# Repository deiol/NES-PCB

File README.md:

# NES-PCB
Based on a request and discussion in this [r/NES thread](https://www.reddit.com/r/nes/comments/1rh8xvy/looking_for_replacement_powereject_boards/), I created a drop-in replacement for the Power/Reset PCB from the front-loader Nintendo Entertainment System.

# PCB Differences
Taking a look at pictures online as well as NES consoles I had available, I realized there are at least two board revisions; NES-SW-01 and NES-SW-02 (if you've come across any other variants, please let me know). 

**NES-SW-01**

**NES-SW-02**

This design is based on the NES-SW-02 as it should be "backwards compatible" with the NES-SW-01.

Additionally, I used the same power switch footprint for the reset switch. This way you should be able to use either switch body type for the reset switch (although you'll want to use a momentary switch for reset, latching for power).

# Board Production
Board thickness is 1.6mm. [Gerber and drill files](https://github.com/deiol/NES-PCB/tree/main/Gerbers) are included in case they are helpful to anyone. They were created for production at JLCPCB following their gudiance on [generating Gerber and Drill files in KiCAD 9](https://jlcpcb.com/help/article/how-to-generate-gerber-and-drill-files-in-kicad-9). I only reference JLCPCB because I have used them in the past. You can of course have the board produced by a different manufacturer, some aspects of the board may need to be tweaked based on *their* requirements.

If you don't want to go through the trouble of getting boards manufactured, they are available for sale on [Tindie](https://www.tindie.com/products/deiol/nes-replacement-powerreset-switch-pcb/) or [Ko-fi](https://ko-fi.com/s/01c29a42ff)

# Disclaimer
I am not an electrical engineer, just a hobbyist. I couldn't find datasheets for any of the components, so the footprints were created from "scratch" using measurements taken with rulers and calipers. Similarly, the boards were measured with rulers and calipers and also compared against scans I took. Everything in this repo is offered as-is, use at your own risk.

**2026-06-15** - I am currently working on another version of the board that will support aftermarket switches. I was hoping to be able to design a single board that would support both native and aftermarket switches. However, due to the way the native switches and board mount to the NES shell, this is not likely to be possible.

**2026-05-07** - The board has been tested by multiple parties with no issues reported! Boards are available for sale on [Tindie](https://www.tindie.com/products/deiol/nes-replacement-powerreset-switch-pcb/) or [Ko-fi](https://ko-fi.com/s/01c29a42ff). 

**2026-03-19** - ~~Currently the board design is untested,~~ I plan on ordering some prototypes and will update this repo after I see how they turn out. I will try to make any adjustments to the files as needed.

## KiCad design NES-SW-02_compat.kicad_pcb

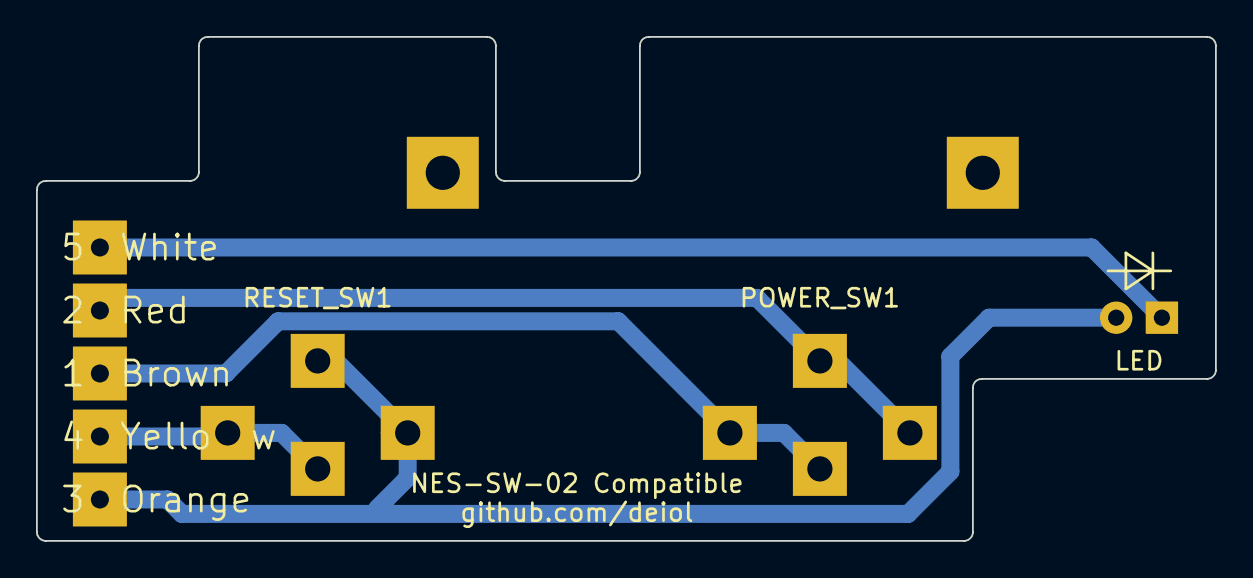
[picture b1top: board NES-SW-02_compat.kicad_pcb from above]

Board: 2 copper layers, 65.5 x 28.0 mm, 4 parts (0 on the bottom side), 5 nets.

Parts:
J1: Conn_01x05; NES-SW-02 Connector
LED: LED; LED_D5.0mm
POWER_SW1: SW_SPST; NES-SW-02 Switch
RESET_SW1: SW_SPST; NES-SW-02 Switch

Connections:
unnamed: J1.1, POWER_SW1.1 (A)
unnamed: J1.2, POWER_SW1.2 (B)
unnamed: J1.3, LED.2 (A), RESET_SW1.2 (B)
unnamed: J1.4, RESET_SW1.1 (A)
unnamed: J1.5, LED.1 (K)

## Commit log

2026-03-20 Fixed URLs in README
2026-06-15 Added notes about completed testing and links to purchase PCBs on Tindie or Ko-fi
2026-06-15 Fixed FUNDING.yml links
2026-06-15 Fixed ko-fi link in README
